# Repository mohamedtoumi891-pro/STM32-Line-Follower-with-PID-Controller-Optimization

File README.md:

# STM32-Line-Follower-with-PID-Controller-Optimization — BACHAWANGUI

> **BACHAWANGUI** is a fully autonomous line-following robot designed and built from scratch for the **ROBOCUP ENSI 7.0** competition. The project encompasses mechanical design (SolidWorks), custom PCB design (KiCad), embedded firmware (PID control), and 3D component modeling.

---

## 📸 PCB Design & Wiring Schematic

<p align="center">
  
  &nbsp;&nbsp;
  
</p>

<p align="center">
  <em>Left: Custom PCB layout (KiCad) — STM32 Blue Pill, L298N, Battery, N20 Motors &amp; IR Sensors integrated</em><br/>
  <em>Right: Full wiring schematic — sensor array, MCU, motor driver &amp; power connections</em>
</p>

---

## 📌 Abstract

In this project, a modified PID controller and open-loop control mechanisms were implemented to improve the stability and robustness of a differential wheeled robot. A test platform was constructed using low-cost, off-the-shelf components including a microcontroller, IR reflectance sensors, and a motor driver. This document describes the heuristic approach used for system identification and controller optimization. The PID controller is analyzed in detail, with the effect of each term explained in the context of line-following stability. Challenges encountered during hardware and software development are also discussed.

---

## 🏗️ Project Architecture

```
BACHAWANGUI/
│
├── ⚙️  Mécanique     → Chassis design (SolidWorks), MDF cutting, assembly
├── ⚡  Électrique     → Wiring, sensor integration, motor connections
├── 💻  Informatique  → PID firmware (Arduino C++), strategy selection
└── 🖥️  PCB Design    → Custom PCB (KiCad), 3D footprints from scratch
```

---

## 🧩 Components

| Component | Description | Quantity |
|-----------|-------------|----------|
| **STM32 Blue Pill** (STM32F103C8) | Main MCU — later replaced by Arduino Mega | 1 |
| **Arduino Mega** | Final competition MCU | 1 |
| **N20 DC Motors** | Micro gear motors (6V) | 2 |
| **IR Sensors** | Infrared line detection sensors | 6 |
| **L298N Motor Driver** | Dual H-bridge motor driver module | 1 |
| **Carte de Puissance** | Custom power management board | 1 |
| **Battery Pack (3× AA)** | 4.5V power supply | 1 |
| **Scroll wheel** | Front passive caster wheel | 1 |
| **MDF Chassis** | Custom-cut wooden frame | 1 |

---

## 🖥️ Software Stack

| Layer | Tool / Framework |
|-------|-----------------|
| Mechanical CAD | SolidWorks |
| PCB Design | KiCad |
| 3D Component Modeling | SolidWorks / KiCad 3D |
| Embedded Firmware | Arduino C++ / STM32 HAL (C) |
| Schematic Design | KiCad Schematic Editor |

---

## 🔌 Wiring & Schematic

The wiring connects 6 independent IR sensors to the microcontroller's digital inputs (PA0–PA5), which runs a PID control loop and outputs PWM signals to the L298N motor driver (via PB0, PB1, PB6, PB7), which in turn drives the two N20 motors.

```
[6× IR Sensors] ──(OUT)──► [STM32 / Arduino Mega]
                                     │
                              [PID Algorithm]
                                     │
                            [L298N Motor Driver]
                               /            \
                       [N20 Motor L]    [N20 Motor R]
                       
[Battery Pack] ──(+4.5V)──► [L298N 12V] ──(5V reg.)──► [IR Sensors VCC]
[Battery Pack] ──(GND)   ──► [Common Ground Rail]
```

### Pin Mapping

| STM32 / Arduino Pin | Connected To |
|---------------------|-------------|
| PA0 | IR Sensor 1 — OUT |
| PA1 | IR Sensor 2 — OUT |
| PA2 | IR Sensor 3 — OUT |
| PA3 | IR Sensor 4 — OUT |
| PA4 | IR Sensor 5 — OUT |
| PA5 | IR Sensor 6 — OUT |
| PB0 | L298N — IN1 |
| PB1 | L298N — IN2 |
| PB6 | L298N — IN3 |
| PB7 | L298N — IN4 |
| PA6 | L298N — ENA (PWM) |
| PA7 | L298N — ENB (PWM) |
| 3.3V / 5V | IR Sensors — VCC |
| GND | Common ground |

---

## ⚙️ Mechanical Design

The chassis was designed in **SolidWorks** then cut from **MDF wood**. A rear perpendicular support bracket was attached to hold the motor assembly. Key design constraints followed the **ROBOCUP ENSI 7.0** specifications.

<p align="center">
  <!-- SolidWorks chassis design — see Main_System_Assembly in the dossier -->
</p>

---

## 🖨️ PCB Design

A **custom PCB** was designed in **KiCad** to integrate all components onto a single board, eliminating loose wiring and improving reliability. Key contributions include:

- ✅ **STM32 Blue Pill** — full schematic symbol, PCB footprint, and 3D model created from scratch
- ✅ **N20 Motors** — custom mounting footprint and 3D model
- ✅ **IR Sensors** — custom connector footprint (6× individual sensors)
- ✅ **Power board (Carte de Puissance)** — custom slot and footprint
- ✅ **Battery holders (3× AA)** — custom 3D model and footprint
- ✅ **Scroll wheel** — custom 3D model for spatial validation

> 💡 All custom KiCad library assets are located in `/hardware/lib/`

---

## 🧠 PID Controller

The robot uses a **PID (Proportional-Integral-Derivative)** controller to follow the line with minimal oscillation:

```
error       = sensor_weighted_position − setpoint
correction  = Kp×error + Ki×∫error dt + Kd×d(error)/dt

motor_left  = base_speed + correction
motor_right = base_speed − correction
```

Parameters Kp, Ki, Kd were tuned heuristically during testing sessions. The sensor array of **6 IR sensors** provides a weighted position estimate of the line relative to the robot center.

---

## 📁 Repository Structure

```
BACHAWANGUI/
│
├── firmware/
│   ├── stm32/              # Original STM32 HAL firmware (C)
│   └── arduino/            # Final competition firmware (Arduino C++)
│       └── pid_linefollower.ino
│
├── hardware/
│   ├── schematics/         # KiCad schematic files (.kicad_sch)
│   ├── pcb/                # PCB layout files (.kicad_pcb)
│   ├── lib/                # Custom footprints, symbols & 3D models
│   │   ├── stm32_bluepill/
│   │   ├── n20_motor/
│   │   ├── ir_sensor/
│   │   ├── power_board/
│   │   └── battery_holder/
│   └── gerbers/            # Manufacturing-ready Gerber files
│
├── mechanical/
│   └── solidworks/         # SolidWorks chassis & component files (.SLDPRT)
│
├── docs/
│   ├── robot_photo.jpg        # Robot photo (ROBOCUP competition)
│   ├── DOSSIER-TECHNIQUE.pdf  # Full technical dossier
│   └── Main_System_Assembly/  # SolidWorks 3D assembly files
│
├── PCB_part/                  # KiCad PCB project files
│   ├── *.kicad_pcb
│   ├── *.kicad_sch
│   └── lib/                   # Custom footprints & 3D models
│
├── pcb_design.png             # PCB 3D render (KiCad)
└── schematic.svg              # Wiring schematic diagram
│
└── README.md
```

---

## 🚀 Getting Started

### Requirements

- [Arduino IDE](https://www.arduino.cc/en/software) — for Arduino Mega firmware
- [STM32CubeIDE](https://www.st.com/en/development-tools/stm32cubeide.html) — for STM32 firmware
- [KiCad 7+](https://www.kicad.org/) — for PCB files
- [SolidWorks 2022+](https://www.solidworks.com/) — for mechanical files

### Build & Upload (Arduino)

```bash
# 1. Open firmware/arduino/pid_linefollower.ino in Arduino IDE
# 2. Select: Tools → Board → Arduino Mega 2560
# 3. Select the correct COM port
# 4. Click Upload
```

---

## 🏁 Competition

The **BACHAWANGUI** robot was entered into the **ROBOCUP ENSI 7.0** competition, organized under the **AEROBOTIX** club (robotics & aeronautics pole of INSAT). The robot competed on both straight and curved track segments.

> Mid-development, the STM32 Blue Pill was replaced with an **Arduino Mega** to resolve firmware timing issues under competition deadline pressure. The team adapted rapidly and competed successfully — a real lesson in engineering resilience and adaptability.

---

## 👥 Team & Club

**Club:** [AEROBOTIX](https://www.instagram.com/aerobotix.insat/) — Pôle Robotique & Aéronautique de l'INSAT  
> AEROBOTIX is Tunisia's leading robotics and aeronautics club with 150+ members, 100+ national competition entries, 17 international participations, and 35+ medals.

| Role | Contribution |
|------|-------------|
| PCB Design & Hardware | Custom PCB, KiCad footprints, 3D models |
| Mechanical Design | SolidWorks chassis, MDF fabrication |
| Firmware | PID algorithm, Arduino/STM32 |
| Electronics | Wiring, sensor integration, power management |

---

## 📄 License

This project is licensed under the [MIT License](LICENSE).

---

> *"The best engineering happens when creativity meets constraints."*

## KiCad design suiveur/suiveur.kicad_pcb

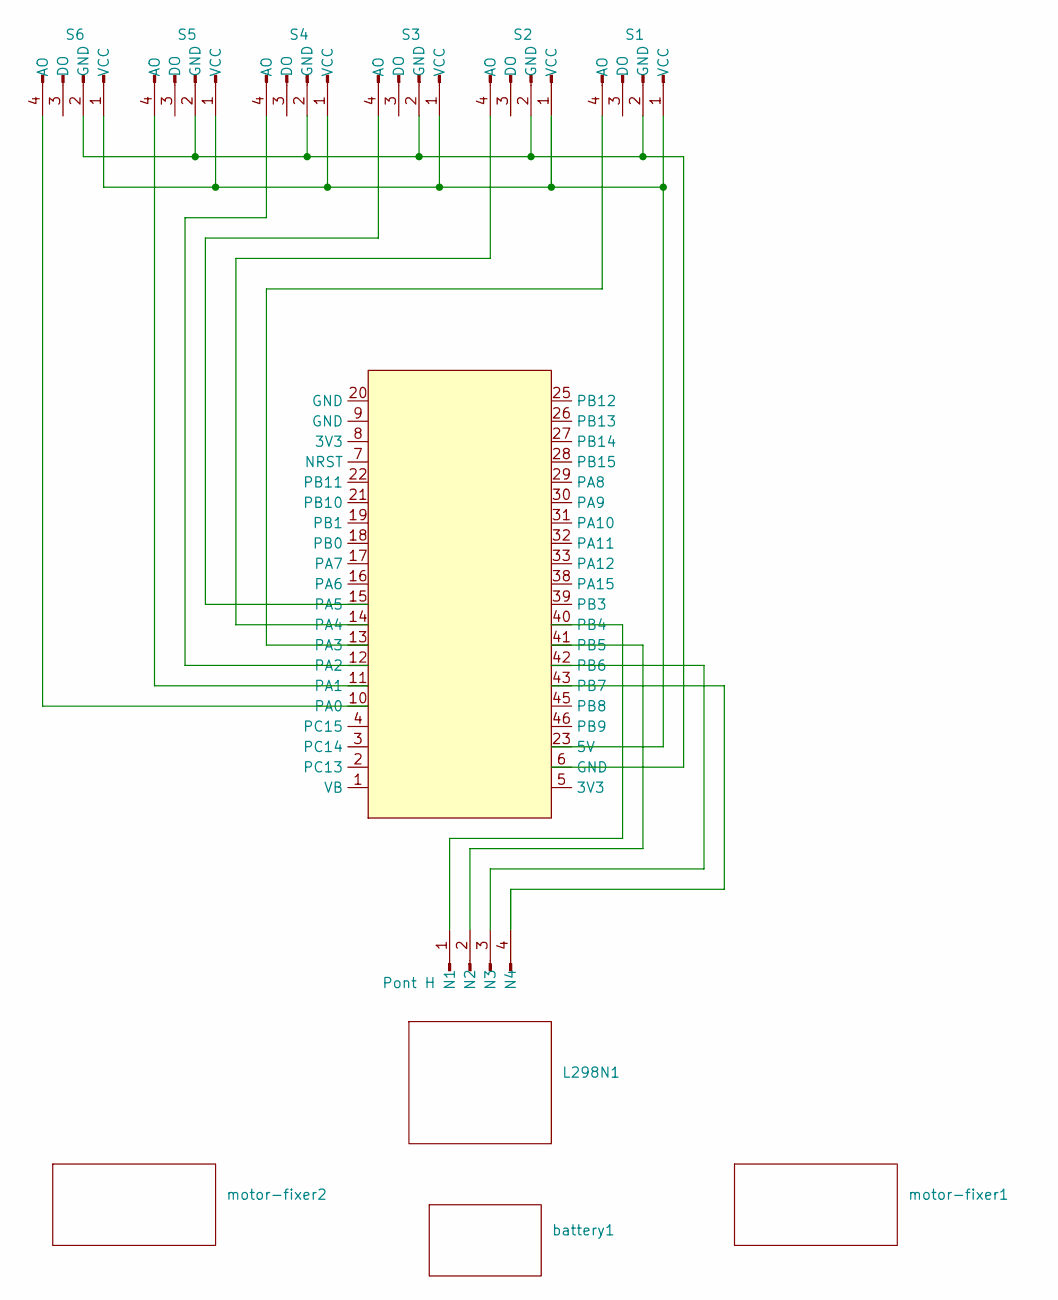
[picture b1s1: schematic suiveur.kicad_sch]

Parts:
L298N1: L289N
P1: Pont H; PinHeader_1x04_P2.54mm_Vertical
S1, S2, S3, S4, S5, S6: TCRT5000; PinHeader_1x04_P2.54mm_Vertical
STM32-BluePill1: stm32 blue pill
battery1: battery
motor-fixer1, motor-fixer2: motor fixer

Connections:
unnamed: P1.1 (N1), STM32-BluePill1.40 (PB4)
unnamed: P1.2 (N2), STM32-BluePill1.41 (PB5)
unnamed: P1.3 (N3), STM32-BluePill1.42 (PB6)
unnamed: P1.4 (N4), STM32-BluePill1.43 (PB7)
unnamed: S1.4 (AO), STM32-BluePill1.13 (PA3)
unnamed: S1.2 (GND), S2.2 (GND), S3.2 (GND), S4.2 (GND), S5.2 (GND), S6.2 (GND), STM32-BluePill1.6 (GND)
unnamed: S1.1 (VCC), S2.1 (VCC), S3.1 (VCC), S4.1 (VCC), S5.1 (VCC), S6.1 (VCC), STM32-BluePill1.23 (5V)
unnamed: S2.4 (AO), STM32-BluePill1.14 (PA4)
unnamed: S3.4 (AO), STM32-BluePill1.15 (PA5)
unnamed: S4.4 (AO), STM32-BluePill1.12 (PA2)
unnamed: S5.4 (AO), STM32-BluePill1.11 (PA1)
unnamed: S6.4 (AO), STM32-BluePill1.10 (PA0)

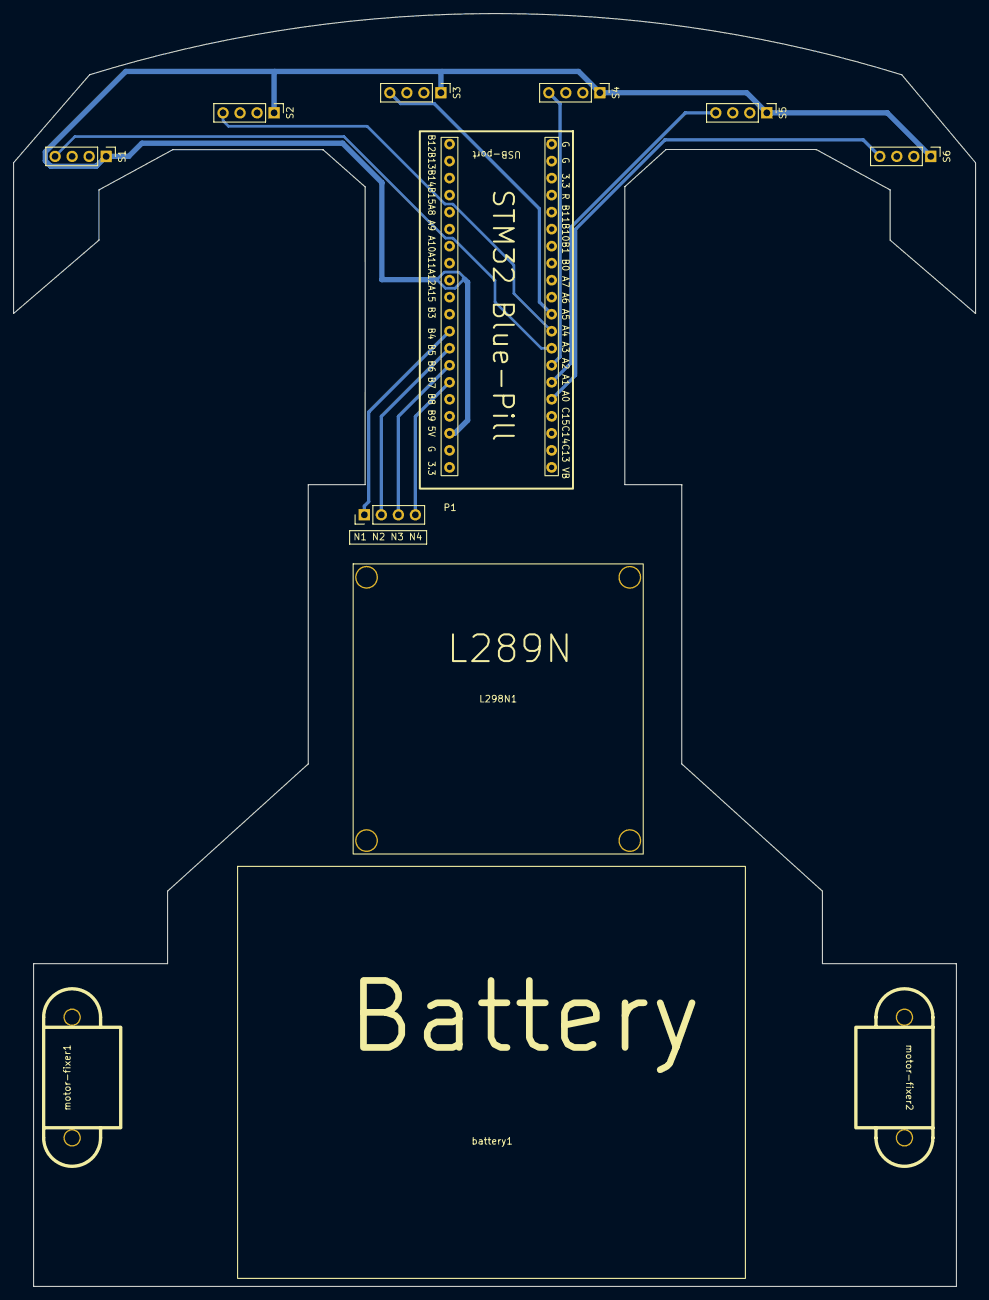
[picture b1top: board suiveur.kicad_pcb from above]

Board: 2 copper layers, 143.6 x 190.0 mm, 12 parts (0 on the bottom side), 12 nets.

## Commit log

2026-04-22 Rename suiveur schematics.png to schematics.png
2026-04-22 Rename schematics.png to schematic.png

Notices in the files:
README.md:
https://img.shields.io/badge/license-MIT-%23F65314?style=flat-square
